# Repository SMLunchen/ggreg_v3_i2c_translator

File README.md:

# GGreg20_V3 → I2C translator (RadSens compatible)

A small board with an ATtiny1614 that counts the pulses of a GGreg20_V3 Geiger counter module and
behaves like a ClimateGuard **RadSens** on the I2C bus (address `0x66`, device ID `0x7D`).
Meshtastic therefore detects the board as a RadSens sensor without any firmware change.

**Status: the firmware compiles and the schematic/PCB pass ERC and DRC, but nothing has been
tested on real hardware yet.** The open points are listed at the bottom.

## Read first: power consumption

The ATtiny draws about 1 µA in sleep (datasheet value). The real consumer is the GGreg20_V3
itself: according to the vendor **35 mA at 5 V, 52 mA at 3.7 V, 57 mA at 3.3 V**, continuously.

The board therefore switches the GGreg20 supply and duty-cycles it by default:

| Mode | GGreg20 on | Average current at 3.3 V |
|---|---|---|
| Low power (default): every 600 s, 15 s warm-up + 60 s measuring | 12.5 % | approx. 7 mA |
| Continuous (`LP_MODE = 0`) | 100 % | approx. 57 mA |

In low-power mode, pulses are only counted during the measuring phases. The 220 s window of
register `0x06` (the one Meshtastic reads) then spans the last almost four measuring phases,
i.e. roughly 37 minutes. That is sufficient for background monitoring, but short events between
measuring phases are missed. Cycle period and measuring time are configurable (see registers
`0x20`–`0x24`).

## Connections

| Connector | Pins (pin 1 = square pad) | Purpose |
|---|---|---|
| J1 `I2C` | VCC, GND, SCL, SDA | to the Meshtastic node, same pinout as RadSens, 3.3 V |
| J3 `PWR` | −, + | switched supply to the GGreg20 ("BAT" connector) |
| J4 `G OUT` | GND, OUT | pulse output of the GGreg20 |
| J5 `VIN` | −, + | optional separate supply for the GGreg20, 3.0–5.5 V |
| J6 `INT` | OUT | GGreg20 pulse passed through unchanged |
| J2 `UPDI` | UPDI, GND, VCC | programming |

All connectors use JST XH footprints (2.5 mm); pin headers or directly soldered wires fit as
well. The labels on the back are placed right next to each pin.

**Solder jumper JP1** selects where the GGreg20 is powered from:

- `VCC` (as delivered, bridged): from the 3.3 V of the I2C connector. The node must then be able
  to supply about 60 mA. Because of its protection diode the GGreg20 needs at least 3.0 V.
- `VIN`: from J5, e.g. directly from the battery or from 5 V. Cut the bridge VCC–centre and
  bridge centre–VIN instead. More efficient, because the GGreg20 draws less current at a higher
  voltage.

The 3.3 V on the I2C connector must be present permanently. If the node switches off the sensor
supply, the ATtiny loses its measurement history and starts over.

## Register overview

RadSens registers (datasheet `RadSens_datasheet_ENG.pdf` and the official Arduino library):

| Address | Content | Access |
|---|---|---|
| `0x00` | Device ID `0x7D` | R |
| `0x01` | Firmware version | R |
| `0x03`–`0x05` | Dose rate, dynamic window (≤ 123 s), 0.1 µR/h, MSB first | R |
| `0x06`–`0x08` | Dose rate, fixed 220 s window, 0.1 µR/h, MSB first | R |
| `0x09`–`0x0A` | Pulse counter, cleared on read, MSB first | R |
| `0x0C` | Low-power mode: 1 = duty-cycled, 0 = continuous | R/W, EEPROM |
| `0x10` | I2C address (`0x03`–`0x77`) | R/W, EEPROM |
| `0x11` | "HV generator": 1 = GGreg20 may run, 0 = off | R/W |
| `0x12`–`0x13` | Sensitivity in pulses/µR, LSB first | R/W, EEPROM |
| `0x14` | On-board LED: 1 = on, 0 = off | R/W, EEPROM |

Extensions specific to this board:

| Address | Content | Access |
|---|---|---|
| `0x20`–`0x21` | Cycle period in s, LSB first (default 600) | R/W, EEPROM |
| `0x22`–`0x23` | Measuring time per cycle in s, LSB first (default 60) | R/W, EEPROM |
| `0x24` | Warm-up time in s (default 15) | R/W, EEPROM |
| `0x25` | Status: bit 0 GGreg20 powered, bit 1 counting, bit 2 window full, bit 3 duty cycling active | R |
| `0x26` | Seconds in the 220 s window | R |
| `0x28`–`0x29` | Seconds remaining in the current phase, LSB first | R |

Calculation as in the RadSens datasheet: `µR/h = pulses × 3600 / (sensitivity × seconds)`.
Sensitivity **105** for the SBM-20 (default), **74** for the J305. 100 µR/h ≈ 1 µSv/h.

Deviations from the original:

- The algorithm of the dynamic window is not described in the datasheet. Here the window
  reaches back until it contains 50 pulses, at most 123 s.
- J6 passes the GGreg20 pulse on directly, not stretched to 11.2 ms.
- If the cycle period is not greater than measuring time + warm-up time, the GGreg20 runs
  continuously.

All defaults are in [firmware/src/config.h](firmware/src/config.h).

## Meshtastic

Nothing to flash: at boot Meshtastic finds the ID `0x7D` at address `0x66` and then reads
register `0x06`. Enable the measurement under *Telemetry → Environment*; the value appears as
"Radiation" in µR/h. After power-up the board reports 0 for about 16 s until the first measured
second is available.

## Firmware

ATtiny1614, bare-metal C, PlatformIO. 2.9 kB flash, 485 bytes RAM.

```
cd firmware
pio run                                  # build
pio run -t upload --upload-port COM5     # flash
```

Programming is done via UPDI with an ordinary USB-serial adapter (SerialUPDI): adapter TX
through 1–4.7 kΩ to UPDI, adapter RX directly to UPDI, plus GND and 3.3 V. The factory fuses are
fine. Flashing erases the EEPROM, so the settings are back at their defaults afterwards.

The ATtiny sleeps in power-down and only wakes up for a pulse, the one-second tick or an I2C
address match. The dose rate is computed only when the host actually reads it. A watchdog (8 s)
and a timeout for stuck I2C transactions prevent the board from blocking the node's bus.

## Hardware

KiCad 9 project in [hardware/](hardware/), 40 × 30 mm, two layers, components on the top side
only.

- [hardware/doc/schematic.pdf](hardware/doc/schematic.pdf), renderings in [hardware/doc/](hardware/doc/)
- Fabrication data in [hardware/fab/](hardware/fab/): `gerber_ggreg_i2c_translator.zip`, `bom.csv`, `positions.csv`

Schematic and PCB are generated from [hardware/gen/design.py](hardware/gen/design.py)
(components, nets, placement; the traces are laid by a small router in the script). After
changing it, regenerate and check everything with:

```
powershell -ExecutionPolicy Bypass -File hardware\gen\build.ps1
```

You can also continue by hand in KiCad, but running the script again will overwrite the files.

Not populated (DNP), only if needed:

- **R1, R2** (4.7 kΩ): I2C pull-ups, in case the node has none.
- **R4** (100 kΩ): pull-up on the pulse input, in case the GGreg20 output has none of its own.
- **Y1, C4, C5**: 32.768 kHz crystal for an accurate time base; also set `USE_XTAL32K 1`.
  Without the crystal the internal oscillator is used, and its error goes directly into the
  dose rate (typically a few percent, more at extreme temperatures).

## Open points before ordering

1. **Pulse output of the GGreg20.** The vendor states 3.0–3.3 V high and "about 0.7 V" low, but
   neither the pulse width nor the output stage. 0.7 V is slightly above the guaranteed low
   level of the ATtiny (0.66 V at 3.3 V), but well below the typical switching threshold. Best
   checked once with an oscilloscope. If the level is not sufficient, R3 is the place to adapt
   it.
2. **Polarity of the GGreg20 connectors.** The datasheet does not say which pin of the two XH
   connectors is pin 1. Check against the labels with a multimeter before plugging in.
3. **Mounting holes.** Two M3 holes 24 mm apart, read from the GGreg20 dimensional drawing, not
   measured.
4. **Warm-up time.** 15 s is derived from the vendor's "10–15 seconds until the first signal"
   and chosen rather conservatively.
5. **Current figures.** ATtiny and GGreg20 currents are datasheet values, not measured.

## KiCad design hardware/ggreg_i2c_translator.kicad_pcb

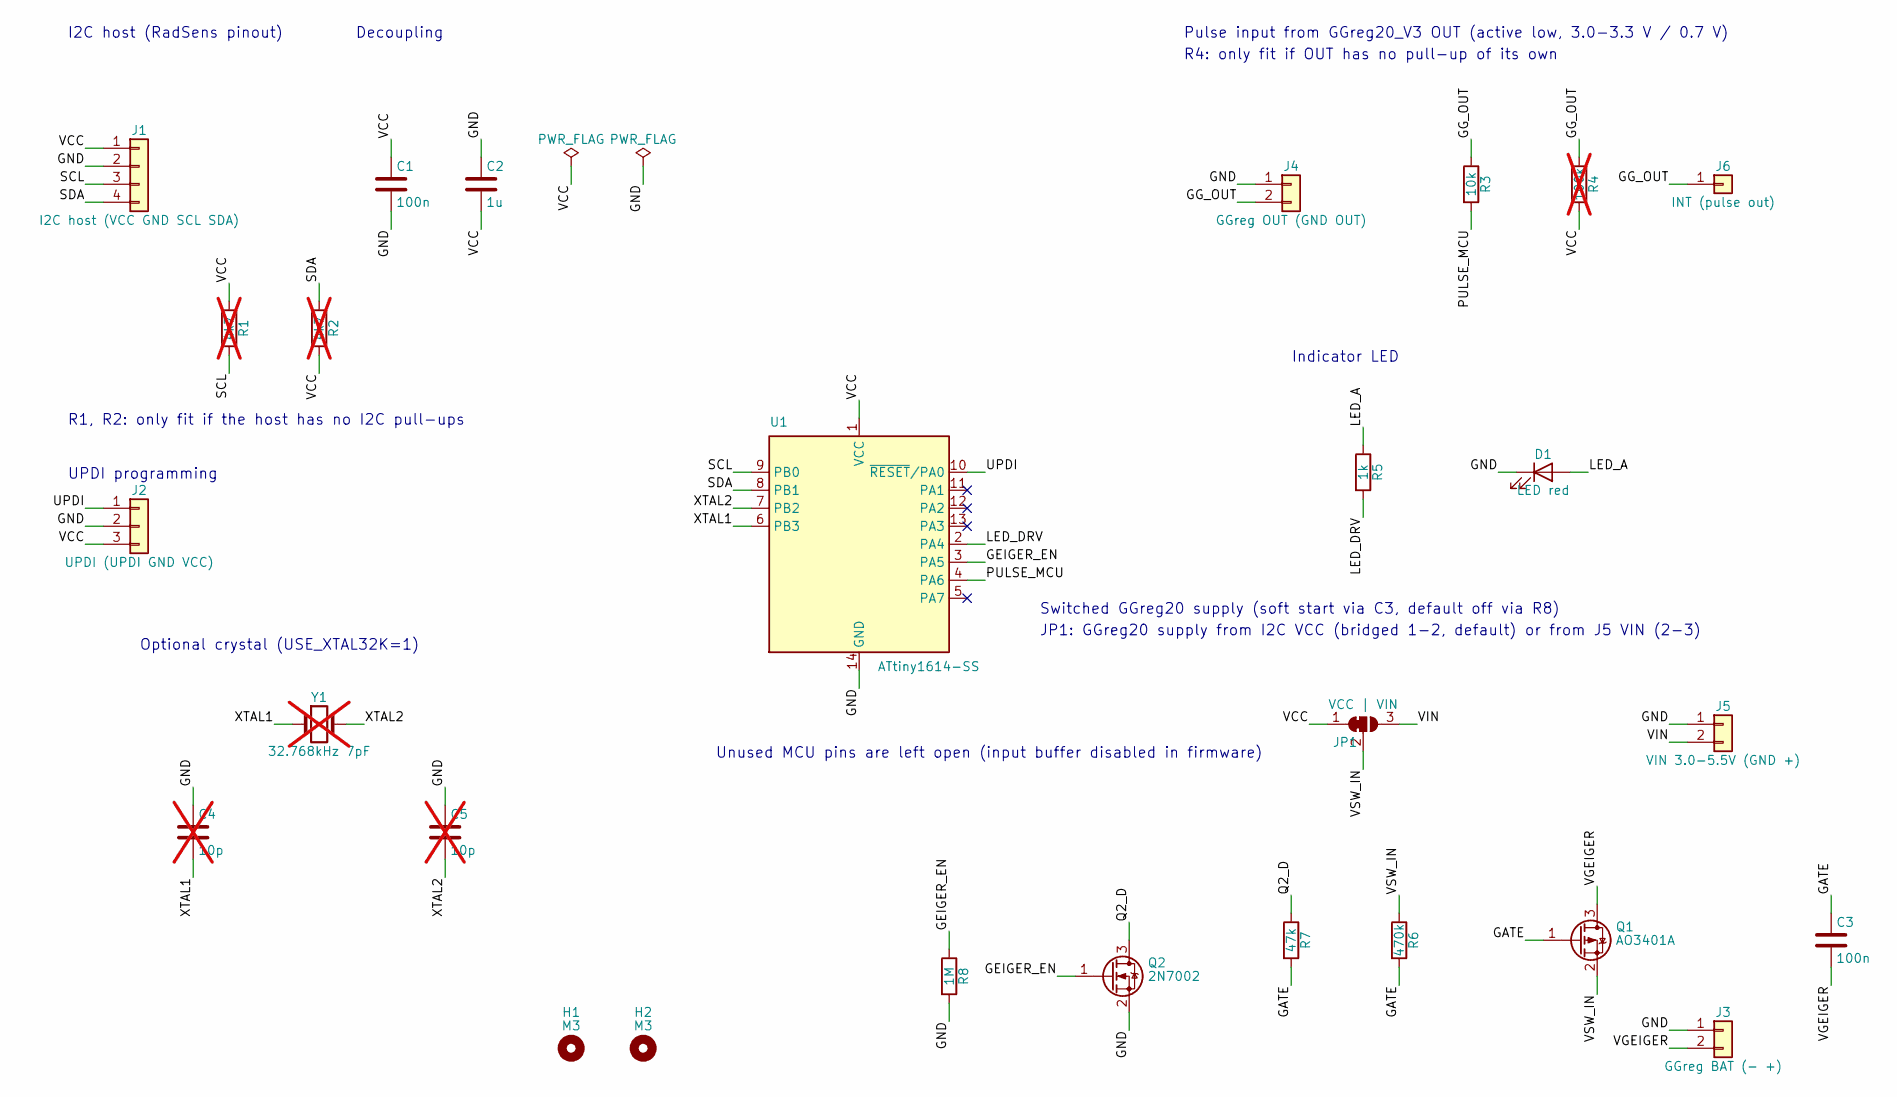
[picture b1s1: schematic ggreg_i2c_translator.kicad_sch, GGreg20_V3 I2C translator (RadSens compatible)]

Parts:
C1, C3: 100n; C_0603_1608Metric
C2: 1u; C_0603_1608Metric
C4, C5: 10p; C_0603_1608Metric; not fitted
D1: LED red; LED_0603_1608Metric
H1, H2: M3; MountingHole_3.2mm_M3
J1: I2C host (VCC GND SCL SDA); JST_XH_B4B-XH-A_1x04_P2.50mm_Vertical
J2: UPDI (UPDI GND VCC); PinHeader_1x03_P2.54mm_Vertical
J3: GGreg BAT (- +); JST_XH_B2B-XH-A_1x02_P2.50mm_Vertical
J4: GGreg OUT (GND OUT); JST_XH_B2B-XH-A_1x02_P2.50mm_Vertical
J5: VIN 3.0-5.5V (GND +); JST_XH_B2B-XH-A_1x02_P2.50mm_Vertical
J6: INT (pulse out); PinHeader_1x01_P2.54mm_Vertical
JP1: VCC | VIN; SolderJumper-3_P1.3mm_Bridged12_RoundedPad1.0x1.5mm
Q1: AO3401A; SOT-23
Q2: 2N7002; SOT-23
R1, R2: 4k7; R_0603_1608Metric; not fitted
R3: 10k; R_0603_1608Metric
R4: 100k; R_0603_1608Metric; not fitted
R5: 1k; R_0603_1608Metric
R6: 470k; R_0603_1608Metric
R7: 47k; R_0603_1608Metric
R8: 1M; R_0603_1608Metric
U1: ATtiny1614-SS; SOIC-14_3.9x8.7mm_P1.27mm
Y1: 32.768kHz 7pF; Crystal_SMD_3215-2Pin_3.2x1.5mm; not fitted

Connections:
/GATE: C3.1, Q1.1 (G), R6.2, R7.2
/GEIGER_EN: Q2.1 (G), R8.1, U1.3 (PA5)
/GG_OUT: J4.2, J6.1, R3.1, R4.1
/GND: C1.2, C2.1, C4.1, C5.1, D1.1 (K), J1.2, J2.2, J3.1, J4.1, J5.1, Q2.2 (S), R8.2, U1.14 (GND)
/LED_A: D1.2 (A), R5.1
/LED_DRV: R5.2, U1.2 (PA4)
/PULSE_MCU: R3.2, U1.4 (PA6)
/Q2_D: Q2.3 (D), R7.1
/SCL: J1.3, R1.2, U1.9 (PB0)
/SDA: J1.4, R2.1, U1.8 (PB1)
/UPDI: J2.1, U1.10 (~RESET/PA0)
/VCC: C1.1, C2.2, J1.1, J2.3, JP1.1 (A), R1.1, R2.2, R4.2, U1.1 (VCC)
/VGEIGER: C3.2, J3.2, Q1.3 (D)
/VIN: J5.2, JP1.3 (B)
/VSW_IN: JP1.2 (C), Q1.2 (S), R6.1
/XTAL1: C4.2, U1.6 (PB3), Y1.1
/XTAL2: C5.2, U1.7 (PB2), Y1.2

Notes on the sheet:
I2C host (RadSens pinout)
Decoupling
R1, R2: only fit if the host has no I2C pull-ups
UPDI programming
Optional crystal (USE_XTAL32K=1)
Pulse input from GGreg20_V3 OUT (active low, 3.0-3.3 V / 0.7 V)
R4: only fit if OUT has no pull-up of its own
Indicator LED
Switched GGreg20 supply (soft start via C3, default off via R8)
JP1: GGreg20 supply from I2C VCC (bridged 1-2, default) or from J5 VIN (2-3)
Unused MCU pins are left open (input buffer disabled in firmware)

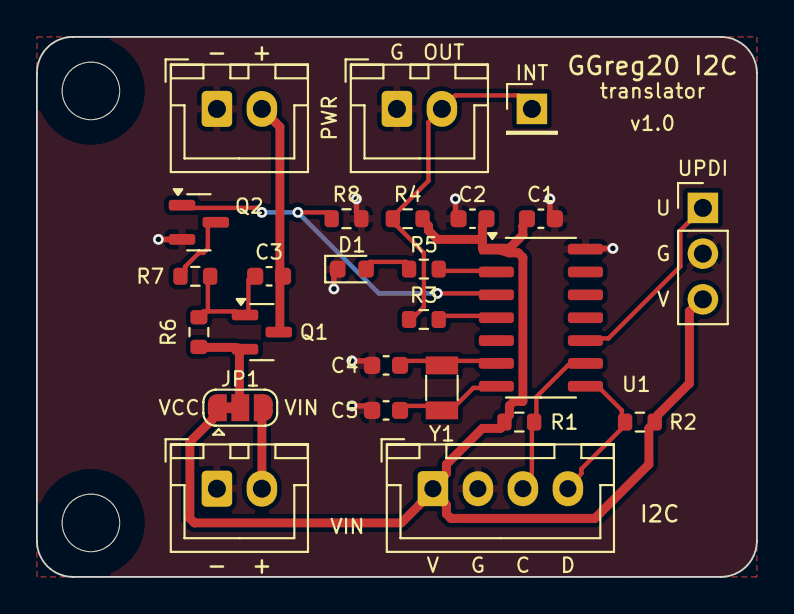
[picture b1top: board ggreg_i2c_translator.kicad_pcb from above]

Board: 2 copper layers, 40.0 x 30.0 mm, 27 parts (0 on the bottom side), 17 nets.

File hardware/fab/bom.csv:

"Refs","Value","Footprint","Qty","DNP"
"C1,C3","100n","Capacitor_SMD:C_0603_1608Metric","2",""
"C2","1u","Capacitor_SMD:C_0603_1608Metric","1",""
"C4,C5","10p","Capacitor_SMD:C_0603_1608Metric","2","Nicht bestücken"
"D1","LED red","LED_SMD:LED_0603_1608Metric","1",""
"J1","I2C host (VCC GND SCL SDA)","Connector_JST:JST_XH_B4B-XH-A_1x04_P2.50mm_Vertical","1",""
"J2","UPDI (UPDI GND VCC)","Connector_PinHeader_2.54mm:PinHeader_1x03_P2.54mm_Vertical","1",""
"J3","GGreg BAT (- +)","Connector_JST:JST_XH_B2B-XH-A_1x02_P2.50mm_Vertical","1",""
"J4","GGreg OUT (GND OUT)","Connector_JST:JST_XH_B2B-XH-A_1x02_P2.50mm_Vertical","1",""
"J5","VIN 3.0-5.5V (GND +)","Connector_JST:JST_XH_B2B-XH-A_1x02_P2.50mm_Vertical","1",""
"J6","INT (pulse out)","Connector_PinHeader_2.54mm:PinHeader_1x01_P2.54mm_Vertical","1",""
"Q1","AO3401A","Package_TO_SOT_SMD:SOT-23","1",""
"Q2","2N7002","Package_TO_SOT_SMD:SOT-23","1",""
"R1,R2","4k7","Resistor_SMD:R_0603_1608Metric","2","Nicht bestücken"
"R3","10k","Resistor_SMD:R_0603_1608Metric","1",""
"R4","100k","Resistor_SMD:R_0603_1608Metric","1","Nicht bestücken"
"R5","1k","Resistor_SMD:R_0603_1608Metric","1",""
"R6","470k","Resistor_SMD:R_0603_1608Metric","1",""
"R7","47k","Resistor_SMD:R_0603_1608Metric","1",""
"R8","1M","Resistor_SMD:R_0603_1608Metric","1",""
"U1","ATtiny1614-SS","Package_SO:SOIC-14_3.9x8.7mm_P1.27mm","1",""
"Y1","32.768kHz 7pF","Crystal:Crystal_SMD_3215-2Pin_3.2x1.5mm","1","Nicht bestücken"

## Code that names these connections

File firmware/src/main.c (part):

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 * Target: ATtiny1614 (tinyAVR 1-series), bare metal, factory fuses.
 *
 * Pins
 *   PA4  LED (active high)
 *   PA5  GEIGER_EN (high = GGreg20 supply switched on)
 *   PA6  PULSE_IN  (GGreg20 OUT, active low; PA6 is a fully asynchronous pin,
 *                   so even very short pulses wake the MCU from power-down)
 *   PB0  SCL, PB1 SDA (TWI client, wakes from power-down on address match)
 *   PB2/PB3 optional 32.768 kHz crystal
 *   PA0  UPDI
 *
 * Power concept
 *   The MCU sits in power-down (~1 uA incl. 1 Hz PIT) and only wakes for
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#endif

/* ---- pins ------------------------------------------------------------- */
#define LED_bm          PIN4_bm         /* PA4 */
#define GEIGER_EN_bm    PIN5_bm         /* PA5 */
#define PULSE_bm        PIN6_bm         /* PA6 */
#define PULSE_PINCTRL   PORTA.PIN6CTRL

#if PULSE_PULLUP
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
